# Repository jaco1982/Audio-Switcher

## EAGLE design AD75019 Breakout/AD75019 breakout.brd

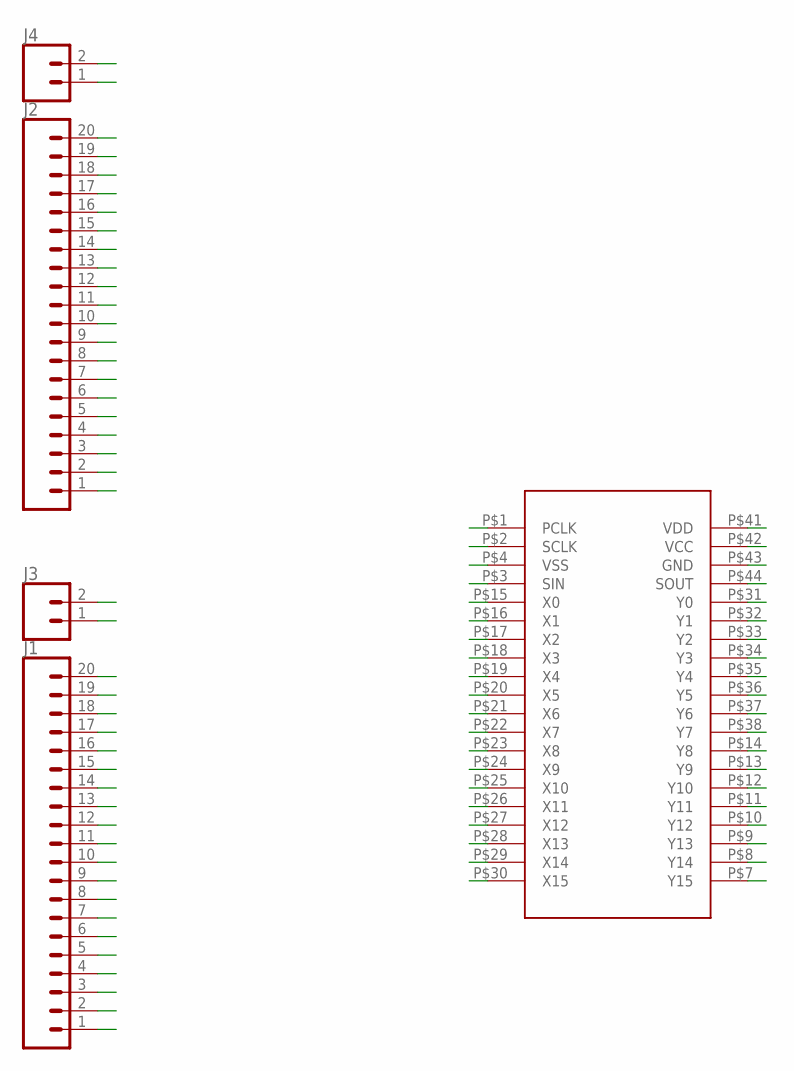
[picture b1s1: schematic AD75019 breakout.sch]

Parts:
J1, J2: CONN_20; 1X20
J3, J4: CONN_02; 1X02
U$1: AD75019DIP44; DIP44

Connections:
1: J1.1, U$1.P$1 (PCLK)
2: J1.2, U$1.P$2 (SCLK)
3: J1.3, U$1.P$3 (SIN)
4: J1.4, U$1.P$4 (VSS)
5: J1.5
6: J1.6
7: J1.7, U$1.P$7 (Y15)
8: J1.8, U$1.P$8 (Y14)
9: J1.9, U$1.P$9 (Y13)
10: J1.10, U$1.P$10 (Y12)
11: J1.11, U$1.P$11 (Y11)
12: J1.12, U$1.P$12 (Y10)
13: J1.13, U$1.P$13 (Y9)
14: J1.14, U$1.P$14 (Y8)
15: J1.15, U$1.P$15 (X0)
16: J1.16, U$1.P$16 (X1)
17: J1.17, U$1.P$17 (X2)
18: J1.18, U$1.P$18 (X3)
19: J1.19, U$1.P$19 (X4)
20: J1.20, U$1.P$20 (X5)
21: J3.1, U$1.P$21 (X6)
22: J3.2, U$1.P$22 (X7)
23: J2.1, U$1.P$23 (X8)
24: J2.2, U$1.P$24 (X9)
25: J2.3, U$1.P$25 (X10)
26: J2.4, U$1.P$26 (X11)
27: J2.5, U$1.P$27 (X12)
28: J2.6, U$1.P$28 (X13)
29: J2.7, U$1.P$29 (X14)
30: J2.8, U$1.P$30 (X15)
31: J2.9, U$1.P$31 (Y0)
32: J2.10, U$1.P$32 (Y1)
33: J2.11, U$1.P$33 (Y2)
34: J2.12, U$1.P$34 (Y3)
35: J2.13, U$1.P$35 (Y4)
36: J2.14, U$1.P$36 (Y5)
37: J2.15, U$1.P$37 (Y6)
38: J2.16, U$1.P$38 (Y7)
39: J2.17
40: J2.18
41: J2.19, U$1.P$41 (VDD)
42: J2.20, U$1.P$42 (VCC)
43: J4.1, U$1.P$43 (GND)
44: J4.2, U$1.P$44 (SOUT)

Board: 2 copper layers, 5 parts (0 on the bottom side), 40 nets, no tracks yet.

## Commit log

2019-01-08 Test upload
    Test upload

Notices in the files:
parts and their libraries:
SparkFun-Connectors: Licensing: Creative Commons ShareAlike 4.0 International - https://creativecommons.org/licenses/by-sa/4.0
